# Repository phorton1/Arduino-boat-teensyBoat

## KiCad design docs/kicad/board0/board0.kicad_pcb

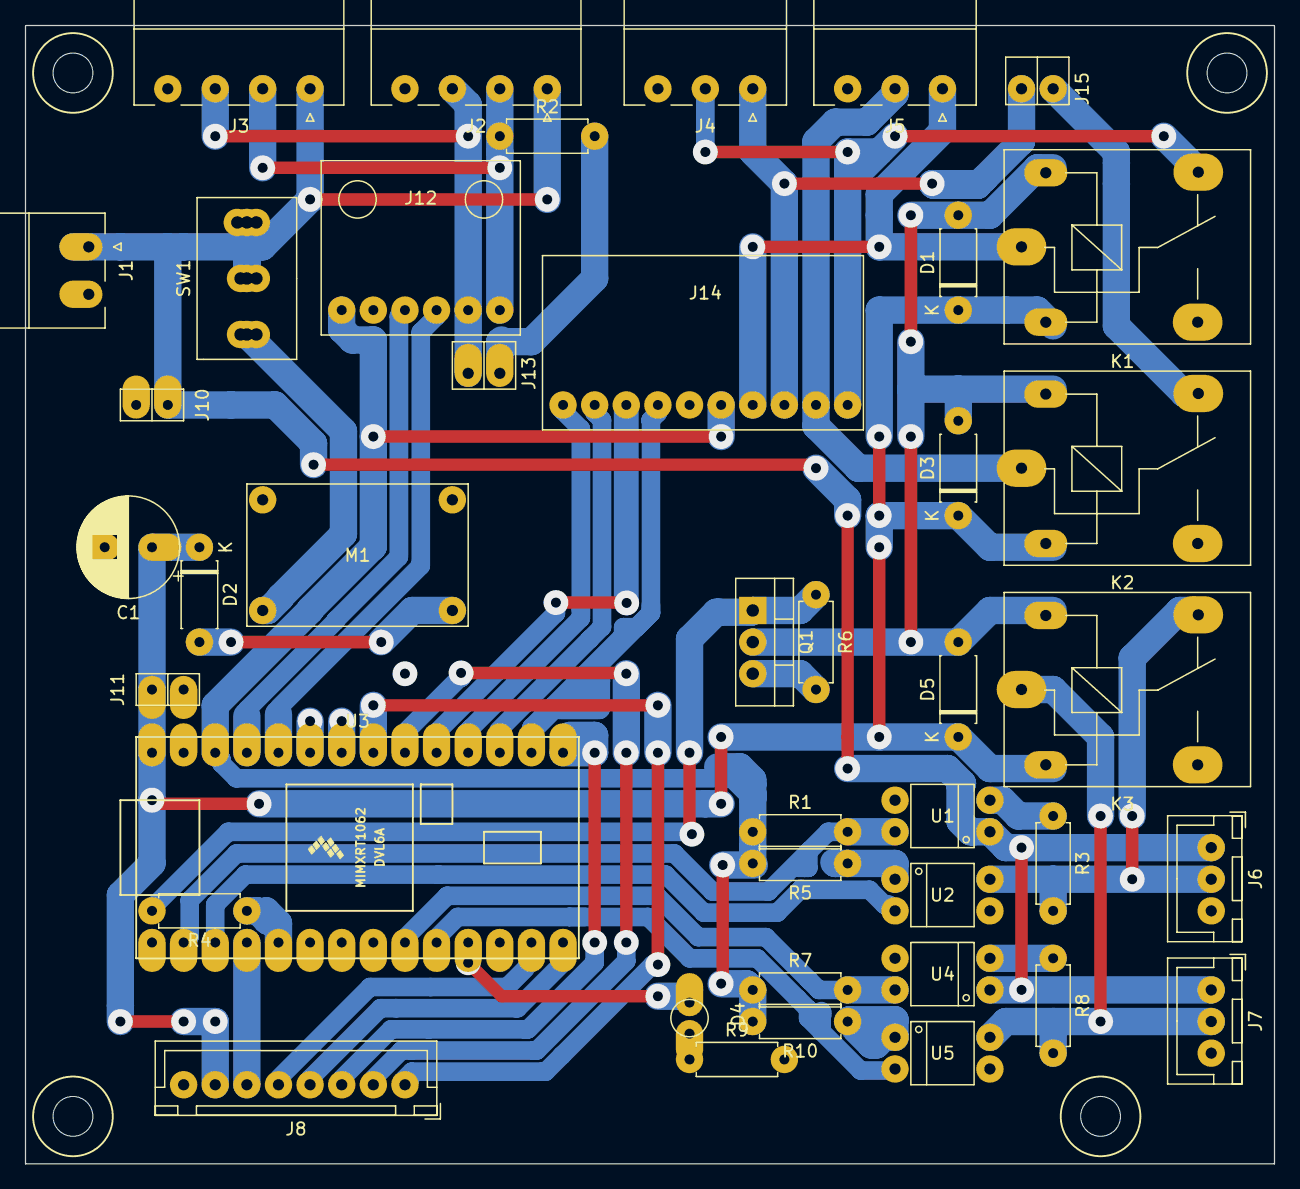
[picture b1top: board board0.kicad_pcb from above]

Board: 2 copper layers, 100.3 x 91.4 mm, 41 parts (0 on the bottom side), 41 nets.

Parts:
C1: 100uf; CP_my100uf
D1, D3, D5: 1N4001; myDiodeSchotsky
D2: 1N5819; myDiodeSchotsky
D4: ALIVE_LED; led_small_red
J1: INST_POWER; myPheonix2x3.81_right
J2, J3: NMEA2000; myPheonix4x3.81_right
J4: 83A; myPheonix3x3.81_right
J5: 83B; myPheonix3x3.81_right
J6: Seatalk1; myJSTx03
J7: Seatalk2; myJSTx03
J8: TEST_RIG; myJSTx08
J10: 12V_TEST; pinSocket1x2
J11: 5V_TEST; pinSocket1x2
J12: SN65HVD230; CANBUS_Module1
J13: CAN_TERMINATOR; pinHeader1x2
J14: MAX3232; MAX3232_Module
J15: GPS_IN; pinHeader1x2
K1: AIS_OUT_RELAY; myRelay2
K2: GPS_IN_RELAY; myRelay2
K3: ST_RELAY; myRelay2
M1: BUCK01; myMini360BuckConverter
Q1: IRLZ44N; myTO-220-3
R1, R3, R7, R8: 4.7K; myResistor
R2: 120; myResistor
R4, R5, R9, R10: 220; myResistor
R6: 10K; myResistor
SW1: POWER; mySwitchToggleSPDT
U1, U4: TLP521-1; myDip4
U2, U5: TLP521-2; myDip4
U3: myTeensy4.0; teensy40

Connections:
83A_IN: J4.2, J14.10, K1.4
83A_OUT: J4.1, J14.8, J15.2
83B_IN: J5.2, J14.9, K2.3
83B_OUT: J5.1, J14.7, K1.3
+3V3: J12.1, J14.6, R1.1, R5.2, R7.1, R10.2, U3.26
+5V: C1.1, D1.1, D2.1, D3.1, D5.1, J8.7, J11.1, K1.2, K2.2, K3.2, U3.28
+12V: J1.1, J2.1, J3.1, J6.1, J7.1, J10.1, SW1.1, SW1.2, U1.1, U4.1
ACTIVE: R4.1, U3.5
ALIVE_LED: D4.2, U3.11
CANH: J2.3, J3.3, J12.5, J13.2
CANL: J2.2, J3.2, J12.6, R2.1
CRX: J12.4, U3.24
CTX: J12.3, U3.25
GND: C1.2, J1.2, J2.4, J3.4, J4.3, J5.3, J6.3, J7.3, J8.8, J10.2, J11.2, J12.2, J14.5, M1.1, M1.2, Q1.3, R6.2, R9.2, U1.3, U2.3, U3.1, U3.27, U4.3, U5.3
unnamed: D2.2, M1.3
unnamed: D4.1, R9.1
unnamed: J13.1, R2.2
unnamed: J15.1, K2.4
unnamed: M1.4, SW1.3
unnamed: Q1.1, R4.2, R6.1
unnamed: R3.1, U1.2
unnamed: R5.1, U2.1
unnamed: R8.1, U4.2
unnamed: R10.1, U5.1
POT_CS1: J8.2, U3.20
POT_CS2: J8.1, U3.21
POT_MISO: J8.4, U3.14
POT_SCLK: J8.3, U3.15
RELAY-: D1.2, D3.2, D5.2, K1.1, K2.1, K3.1, Q1.2
RX1: R1.2, U1.4, U3.2
RX2: R7.2, U3.9, U4.4
RX3: J14.2, U3.17
RX4: J14.1, U3.18
SPEED_PULSE: J8.6, U3.4
ST1: J6.2, K3.4, R3.2, U2.4
ST2: J7.2, K3.3, R8.2, U5.4
TX1: U2.2, U3.3
TX2: U3.10, U5.2
TX3: J14.4, U3.16
TX4: J14.3, U3.19
WIND_PULSE: J8.5, U3.13

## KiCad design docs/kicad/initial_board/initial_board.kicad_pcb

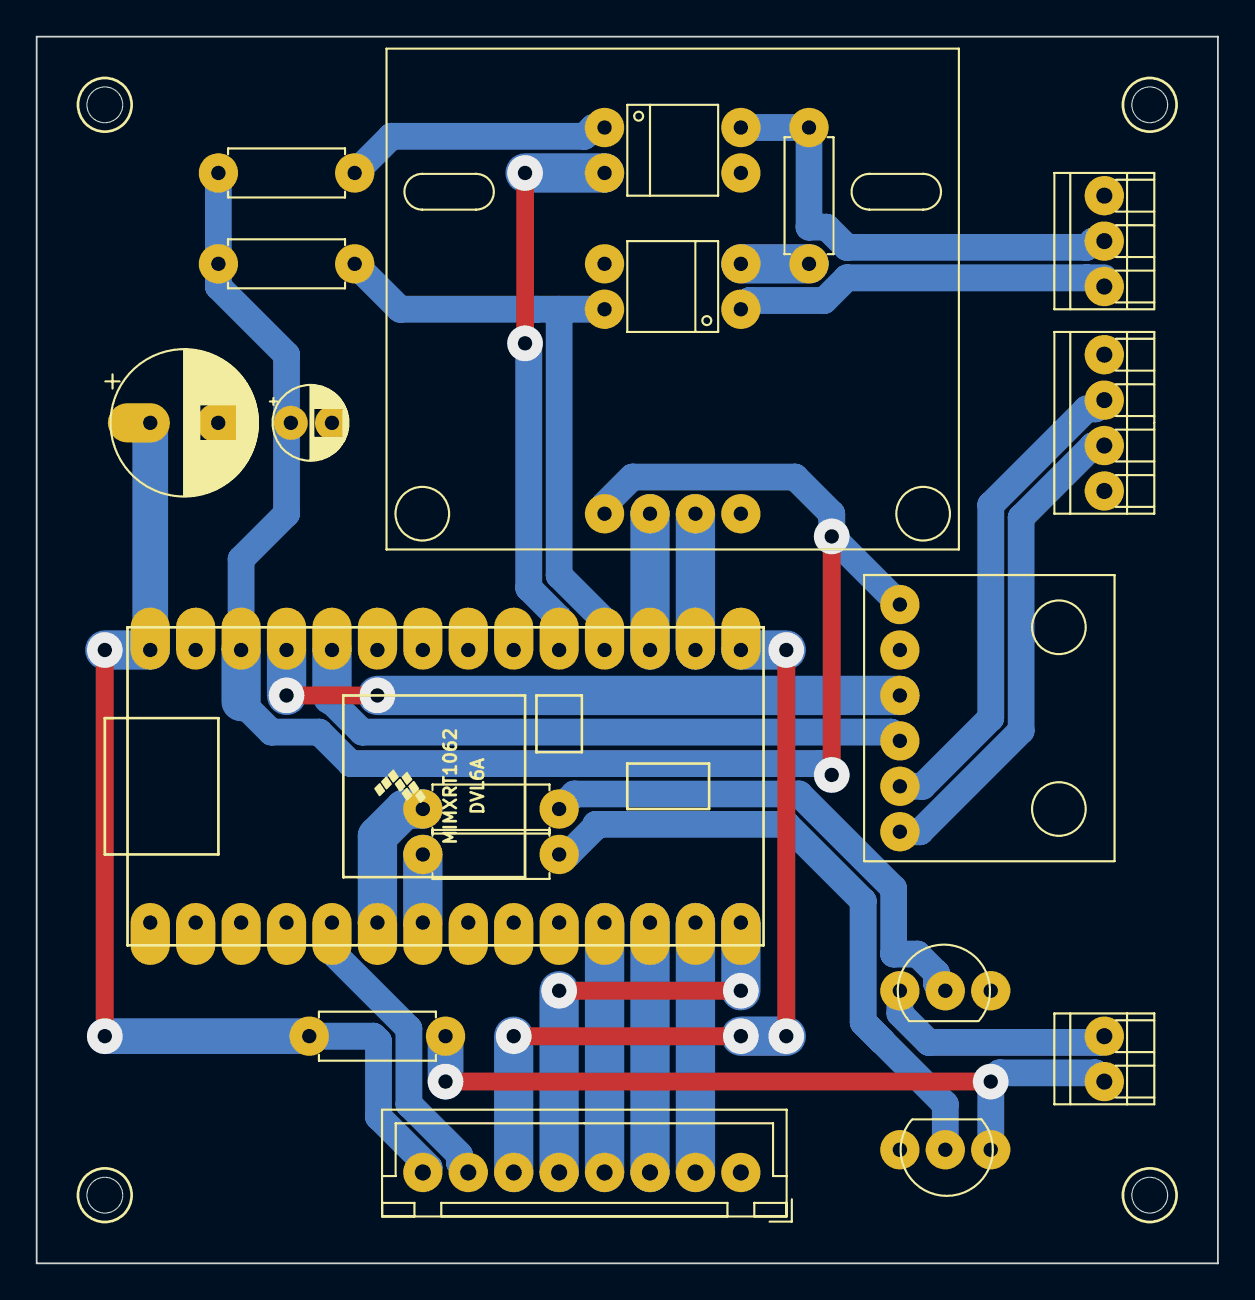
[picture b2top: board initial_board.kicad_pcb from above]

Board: 2 copper layers, 66.0 x 68.6 mm, 19 parts (0 on the bottom side), 27 nets.

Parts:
C1: 47uf; CP_my10uf
C2: 100uf; CP_my100uf
J1: RS232-1; RS232_Module
J2: CAN_MODULE; CANBUS_Module1
J3: NMEA200; myTerminalBlock_2.54x04
J4: Seatalk; myTerminalBlock_2.54x03
J5: TEST_ST50; myTerminalBlock_2.54x02
J6: TE_DISPLAY; myJSTx08
Q1, Q2: BC547; myTransistor
R1, R5: 100; myResistor
R2, R3: 220; myResistor
R4, R6: 4.7K; myResistor
U1: myTeensy4.0; teensy40
U2: TLP521-1; myDip4
U3: TLP521-2; myDip4

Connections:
+3V3: C1.1, J1.1, J2.1, R3.2, R4.1, U1.26
+5V: C2.1, J6.8, R2.2, U1.28
+12V: J4.3, U2.1
CANH: J2.5, J3.2
CANL: J2.6, J3.3
CRX: J2.4, U1.24
CTX: J2.3, U1.25
GND: C1.2, C2.2, J1.4, J2.2, J3.4, J4.1, J6.1, Q1.3, Q2.3, U1.27, U2.3, U3.3
LCD_CS: J6.3, U1.12
LCD_DC: J6.4, U1.11
MISO: J6.5, U1.14
MOSI: J6.2, U1.13
unnamed: J4.2, R6.2, U3.4
unnamed: Q1.2, R1.1
unnamed: Q2.2, R5.1
unnamed: R3.1, U3.1
unnamed: R6.1, U2.2
RX3: J1.2, U1.17
RX4: R4.2, U1.18, U2.4
SCLK: J6.6, U1.15
SPEED_PULSE: R5.2, U1.6
ST50_LOG_GREEN: J5.1, Q2.1
ST50_WIND_YELLOW: J5.2, Q1.1, R2.1
TX3: J1.3, U1.16
TX4: U1.19, U3.2
T_CS: J6.7, U1.5
WIND_PULSE: R1.2, U1.7

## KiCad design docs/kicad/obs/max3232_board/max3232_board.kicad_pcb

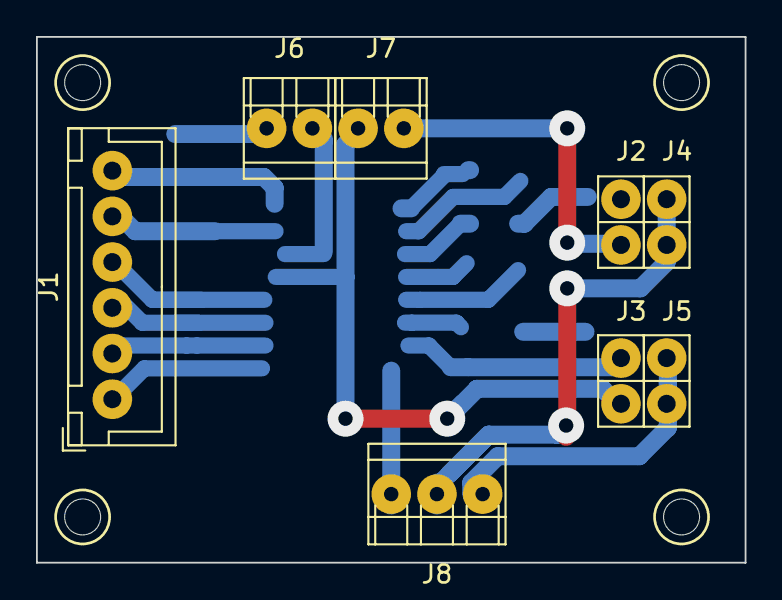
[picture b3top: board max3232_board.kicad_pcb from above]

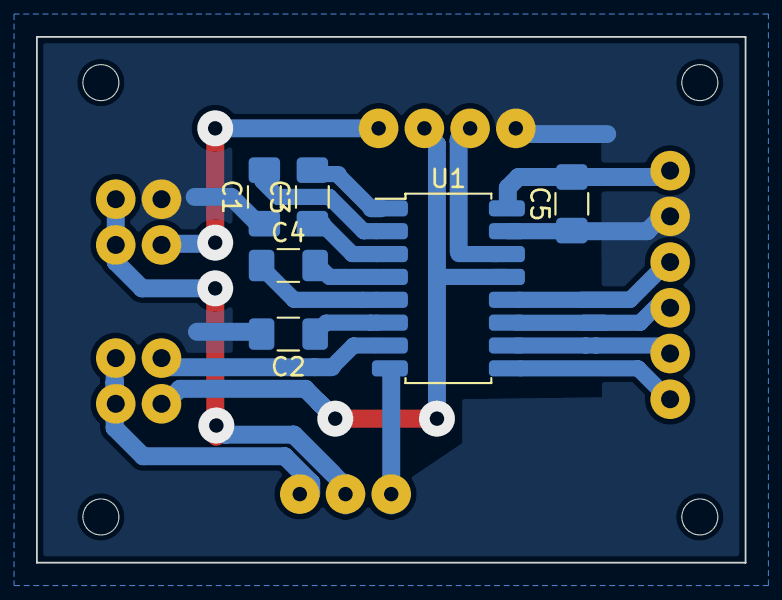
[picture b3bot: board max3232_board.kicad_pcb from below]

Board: 2 copper layers, 39.4 x 29.2 mm, 14 parts (6 on the bottom side), 19 nets.

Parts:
C1, C2, C3, C4, C5: 100nf; C_1206_3216Metric_Pad1.42x1.75mm_HandSolder
J1: Conn_01x06; myJSTx06
J2: JMP1A; myPinHeader_1x02
J3: JMP2A; myPinHeader_1x02
J4: JMP1B; myPinHeader_1x02
J5: JMP2B; myPinHeader_1x02
J6: VHF_0183A; myTerminalBlock_2.54x02
J7: VHF_0183B; myTerminalBlock_2.54x02
J8: E80_0183; myTerminalBlock_2.54x03
U1: MAX3232; SOIC-16_4.55x10.3mm_P1.27mm

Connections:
+3V3: C5.2, J1.6, U1.16
E80-: J4.1, J4.2, J8.2
E80_IN: J5.1, J5.2, J8.1
GND: C1.1, C2.2, C5.1, J1.5, J2.2, J6.1, U1.15
MPU_IN1: J1.3, U1.11
MPU_IN2: J1.2, U1.10
MPU_OUT1: J1.4, U1.12
MPU_OUT2: J1.1, U1.9
unnamed: C1.2, U1.2
unnamed: C2.1, U1.6
unnamed: C3.1, U1.3
unnamed: C3.2, U1.1
unnamed: C4.1, U1.5
unnamed: C4.2, U1.4
RS232_IN1: J7.1, U1.13
RS232_IN2: J8.3, U1.8
RS232_OUT1: J6.2, U1.14
RS232_OUT2: J3.2, U1.7
VHF_AIS-: J2.1, J7.2
